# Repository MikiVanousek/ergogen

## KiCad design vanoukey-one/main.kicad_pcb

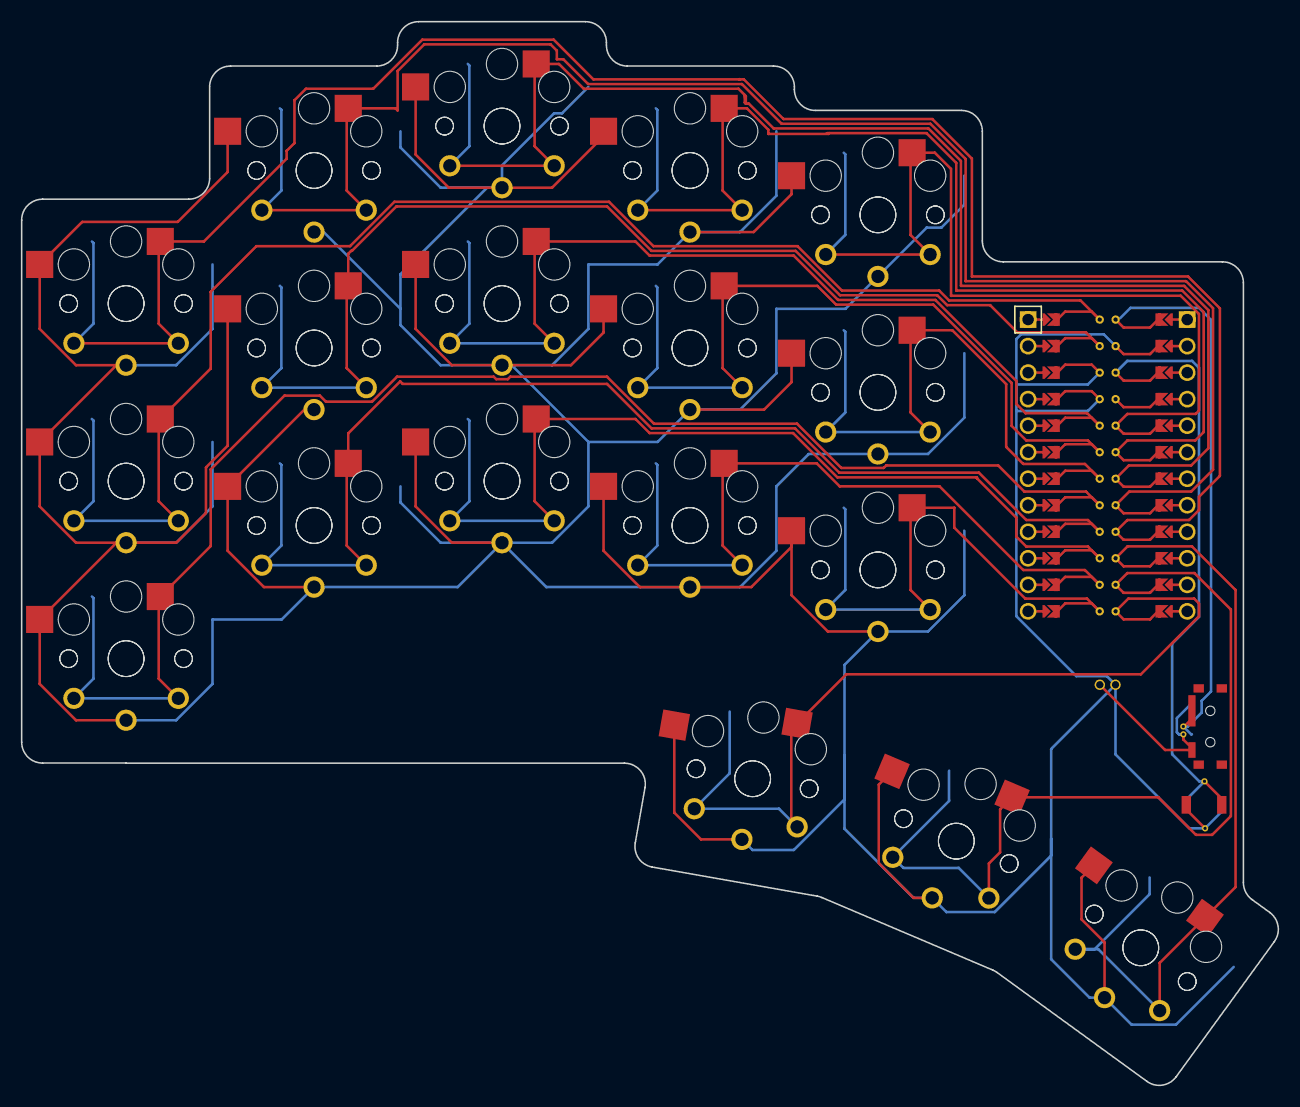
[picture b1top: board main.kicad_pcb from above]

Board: 2 copper layers, 120.3 x 101.9 mm, 37 parts (0 on the bottom side), 19 nets.

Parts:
MCU1: ProMicro
S1, S2, S3, S4, S5, S6, S7, S8, S9, S10, S11, S12, S13, S14, S15, S16, S17, S18, S19, S20, S21, S22, S23, S24, S25, S26, S27, S28, S29, S30, S31, S32, S33, S34, S35, S36: PG1350

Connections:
GND: MCU1.2, MCU1.21, MCU1.22, S1.2, S2.2, S3.2, S4.2, S5.2, S6.2, S7.2, S8.2, S9.2, S10.2, S11.2, S12.2, S13.2, S14.2, S15.2, S16.2, S17.2, S18.2, S19.2, S20.2, S21.2, S22.2, S23.2, S24.2, S25.2, S26.2, S27.2, S28.2, S29.2, S30.2, S31.2, S32.2, S33.2, S34.2, S35.2, S36.2
P0: MCU1.23, S9.1, S10.1
P1: MCU1.24, S3.1, S4.1
P2: MCU1.20, S15.1, S16.1
P3: MCU1.19, S21.1, S22.1
P4: MCU1.18, S27.1, S28.1
P5: MCU1.17, S1.1, S2.1
P6: MCU1.16, S7.1, S8.1
P7: MCU1.15, S13.1, S14.1
P8: MCU1.14, S19.1, S20.1
P9: MCU1.13, S25.1, S26.1
P10: MCU1.12, S31.1, S32.1
P14: MCU1.10, S35.1, S36.1
P15: MCU1.9, S5.1, S6.1
P16: MCU1.11, S33.1, S34.1
P18: MCU1.8, S11.1, S12.1
P19: MCU1.7, S17.1, S18.1
P20: MCU1.6, S23.1, S24.1
P21: MCU1.5, S29.1, S30.1

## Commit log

2022-05-01 ben's config compiles
2022-05-01 fix indentation
2022-05-01 created simon's config
2022-05-22 1st try at changing layout
2022-05-30 change column net
2022-05-30 finished route design
2022-05-30 refactor
2022-09-20 mikikey-one
2022-09-20 add output
